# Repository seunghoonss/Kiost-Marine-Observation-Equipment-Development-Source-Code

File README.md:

Kiost Marine Observation Equipment Development Source Code

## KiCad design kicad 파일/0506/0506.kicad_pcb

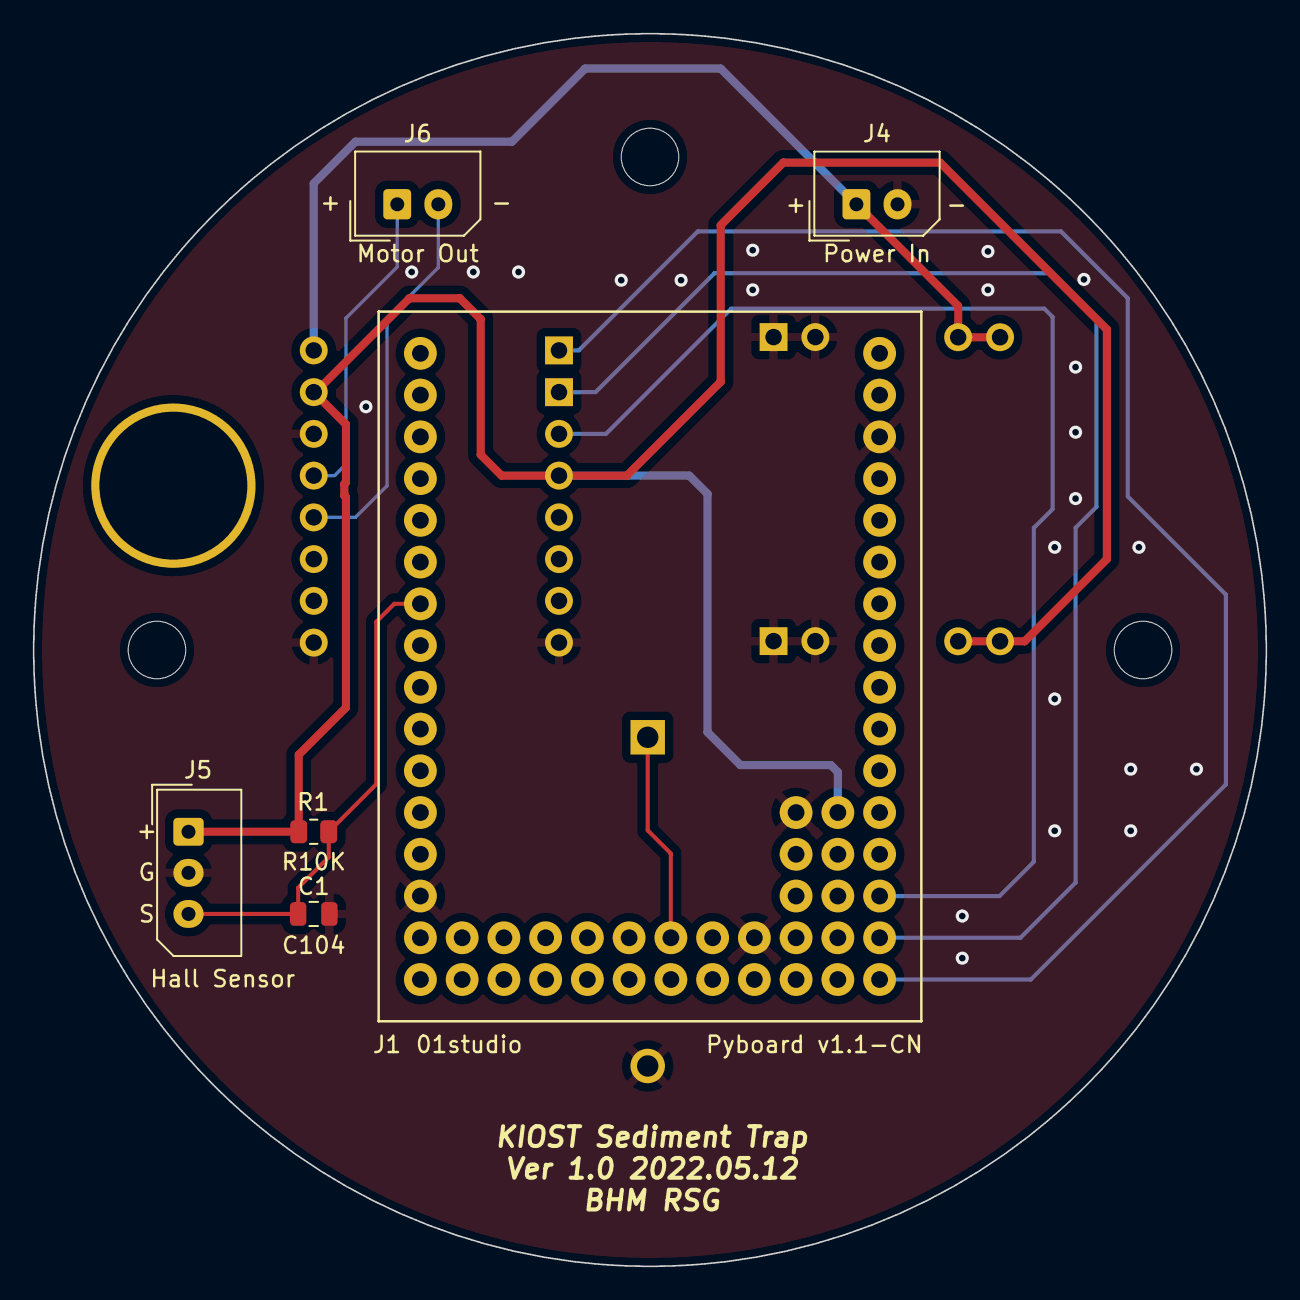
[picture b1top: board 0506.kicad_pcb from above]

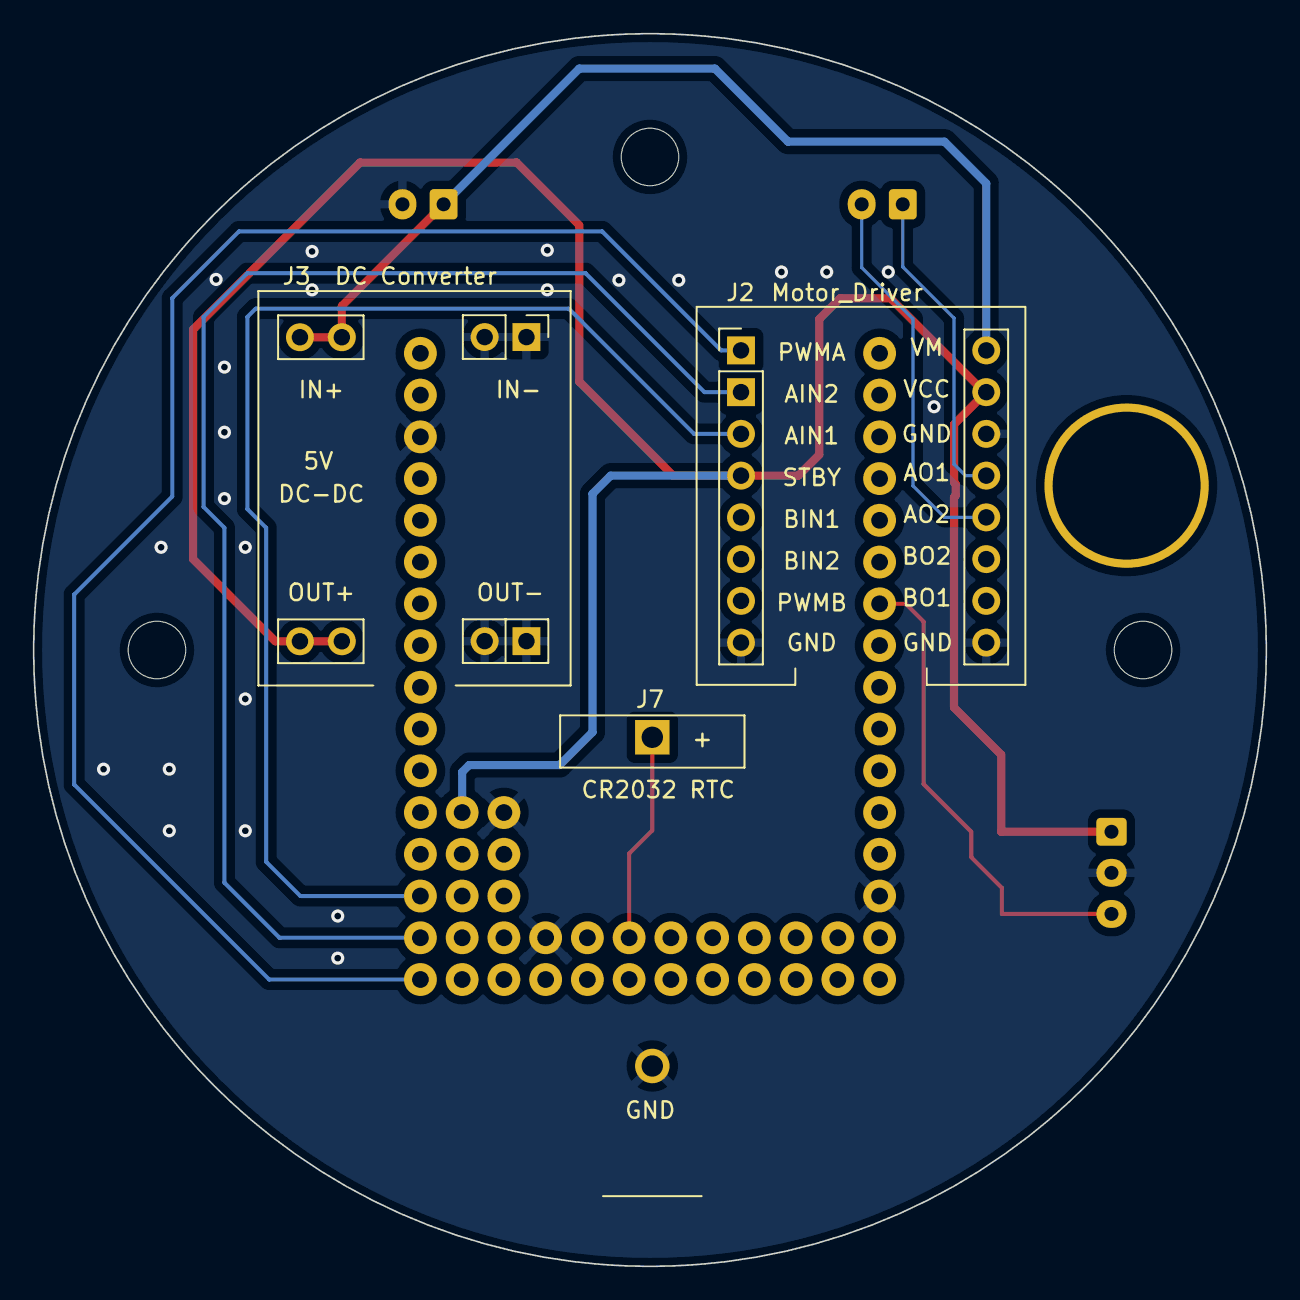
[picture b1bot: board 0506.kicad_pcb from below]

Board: 2 copper layers, 75.0 x 75.0 mm, 13 parts (3 on the bottom side), 10 nets.

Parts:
C1: C104; C_0805_2012Metric
H1: MountingHole_3.2mm_1; MountingHole_3.5mm
H2: MountingHole_3.2mm_2; MountingHole_3.5mm
H3: MountingHole_10mm; Connector Hole 10mm
H4: MountingHole_3.2mm_4; MountingHole_3.5mm
J1: Pyboard v1.1-CN; pyboard_v1.1
J2: Motor_Driver; TB6612FNG
J3: DC Converter; DCDC
J4: Power In; Molex_SPOX_5267-02A_1x02_P2.50mm_Vertical
J5: Hall Sensor; Molex_SPOX_5267-03A_1x03_P2.50mm_Vertical
J6: Motor Out; Molex_SPOX_5267-02A_1x02_P2.50mm_Vertical
J7: CR2032 RTC; BatteryHolder_ComfortableElectronic_CH273-2450_1x2450
R1: R10K; R_0805_2012Metric

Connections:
+5V: J1.P10E (VBAT), J2.4 (STBY), J2.15 (VCC), J3.5 (OUT+), J3.6 (OUT+), J5.1, R1.2
+12V: J2.16 (VMOT), J3.3 (IN+), J3.4 (IN+), J4.1 (12V)
/AIN1: J1.X3 (PA2/TX2/ADC/PWM/SERVO), J2.3 (AIN1)
/AIN2: J1.X2 (PA1/RX4/ADC/PWM/SERVO), J2.2 (AIN2)
/Motor+: J2.13 (AO1), J6.1
/Motor-: J2.12 (AO2), J6.2
/PWMA: J1.X1 (PA0/TX4/ADC/PWM/SERVO), J2.1 (PWMA)
/SIG: C1.1, J1.Y7 (PB14/MISO2/PWM), J5.3, R1.1
GND: C1.2, J1.P8 (GND), J1.P9E (GND), J1.X14 (GND), J1.Y14 (GND), J2.8 (GND), J2.9 (GND), J2.14 (GND), J3.1 (IN-), J3.2 (IN-), J3.7 (OUT-), J3.8 (OUT-), J4.2 (GND), J5.2, J7.2 (-)
unnamed: J1.P6 (VBACK), J7.1 (+)

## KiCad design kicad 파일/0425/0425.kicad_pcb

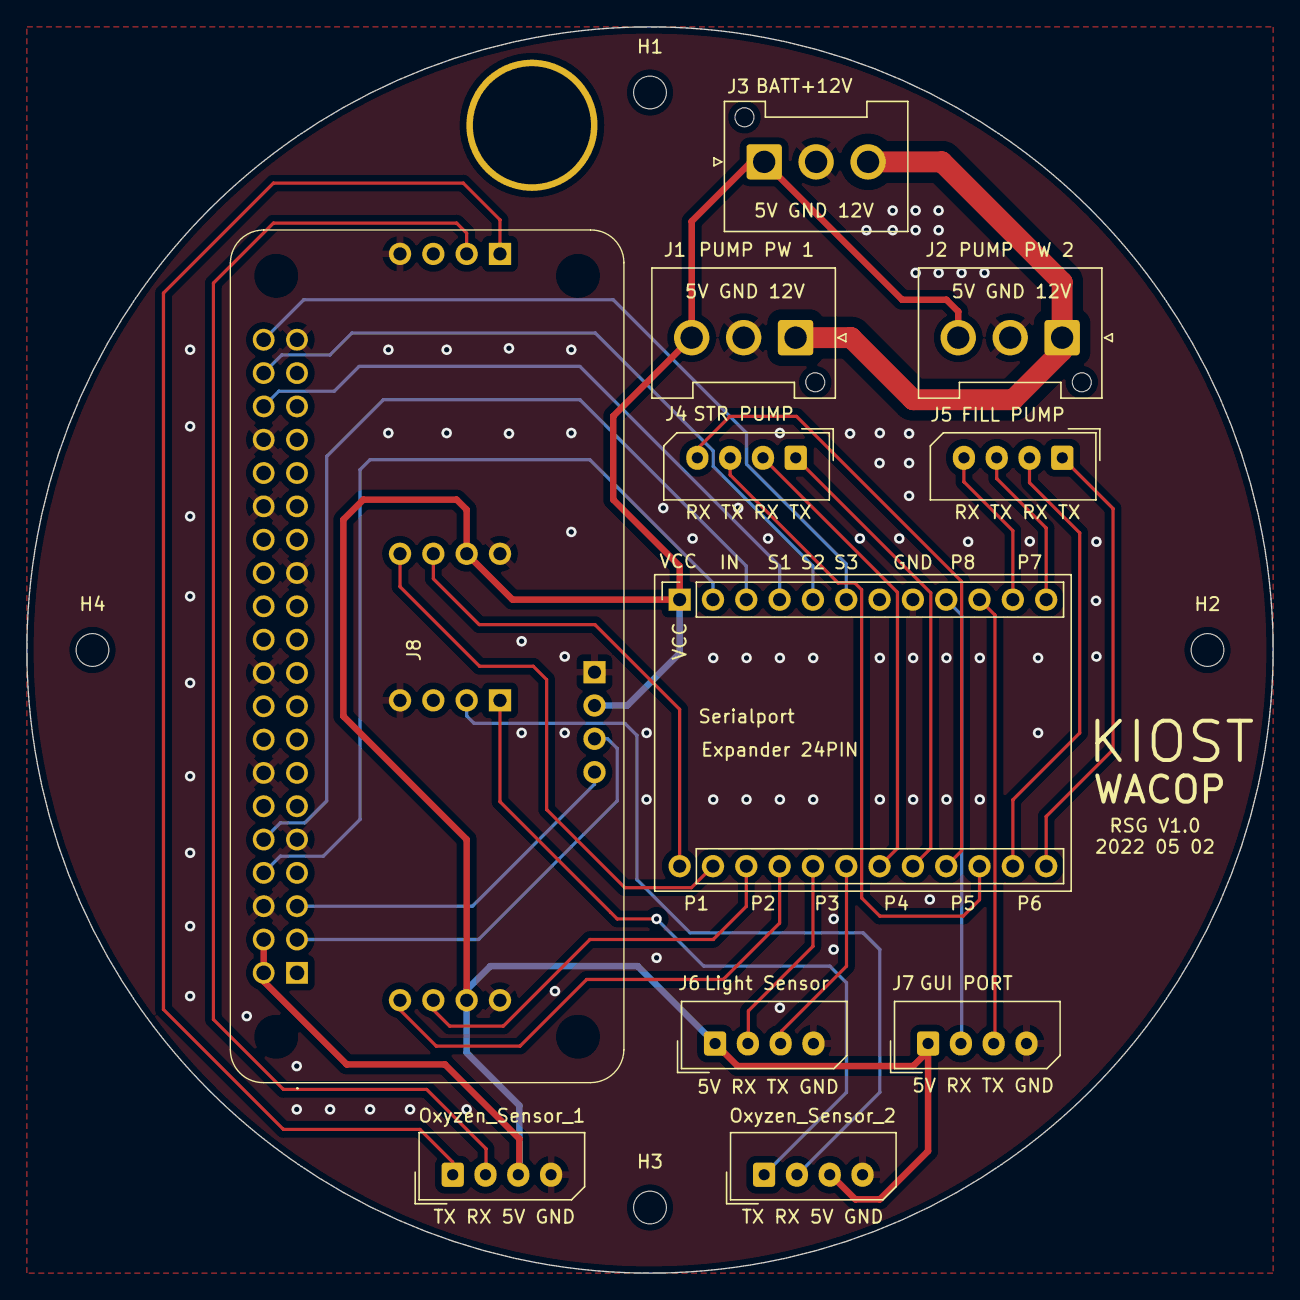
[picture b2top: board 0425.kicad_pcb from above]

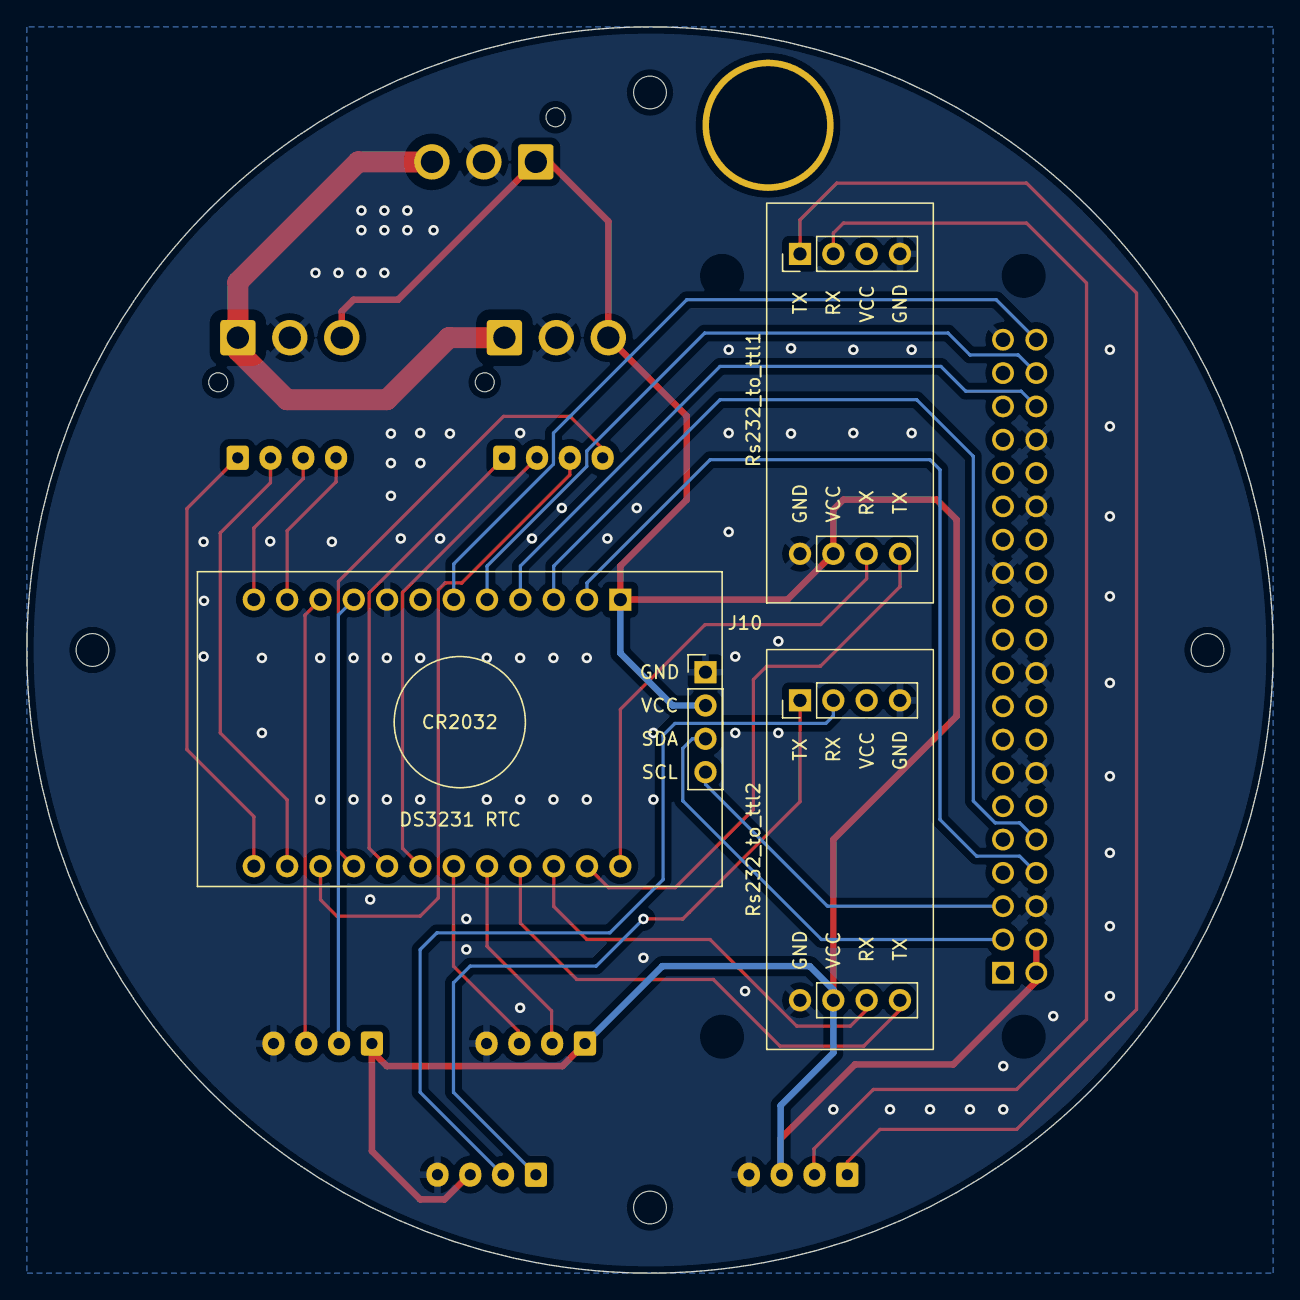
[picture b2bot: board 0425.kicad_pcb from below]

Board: 2 copper layers, 95.0 x 95.0 mm, 19 parts (3 on the bottom side), 30 nets.

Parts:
H1, H2, H3, H4: MH 2.5mm; MountingHole_2.5mm
H5: CH 10mm; Connector Hole 10mm
J1: P_Out_1; JST_VH_B3P-VH-FB-B_1x03_P3.96mm_Vertical
J2: P_Out_2; JST_VH_B3P-VH-FB-B_1x03_P3.96mm_Vertical
J3: Power_IN; JST_VH_B3P-VH-FB-B_1x03_P3.96mm_Vertical
J4: Stir_Motor_RXTX; Molex_SPOX_5267-04A_1x04_P2.50mm_Vertical
J5: Fill_Motor_RXTX; Molex_SPOX_5267-04A_1x04_P2.50mm_Vertical
J6: Light_Sensor; Molex_SPOX_5267-04A_1x04_P2.50mm_Vertical
J7: GUI_PORT; Molex_SPOX_5267-04A_1x04_P2.50mm_Vertical
J8: RaspberryPi_Zero_2_W; Zero_2
J9: SerialPortExpander; serialport expander 2x12pin 2.54mm
J10: Ds3231_RTC; DS3231_RTC
Oxyzen_Sensor_1, Oxyzen_Sensor_2: Conn_01x04; Molex_SPOX_5267-04A_1x04_P2.50mm_Vertical
Rs232_to_ttl1, Rs232_to_ttl2: Conn_02x04_Counter_Clockwise; Rs232 to TTL

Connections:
+5V: J1.3, J2.3, J3.1, J6.1, J7.1, J8.2, J8.4, J9.1 (VCC), J10.2, Oxyzen_Sensor_1.3, Oxyzen_Sensor_2.3, Rs232_to_ttl1.2 (VCC), Rs232_to_ttl2.2 (VCC)
+12V: J1.1, J2.1, J3.3
/RX-IN: J8.8, J9.2 (RX-IN)
/RX-P1: J9.13 (RX-P1), Rs232_to_ttl1.3 (RX)
/RX-P2: J9.15 (RX-P2), Rs232_to_ttl2.3 (RX)
/RX-P3: J6.2, J9.17 (RX-P3)
/RX-P4: J4.2, J9.19 (RX-P4)
/RX-P5: J4.4, J9.21 (RX-P5)
/RX-P6: J5.2, J9.23 (RX-P6)
/RX-P7: J5.4, J9.11 (RX-P7)
/RX-P8: J7.2, J9.9 (RX-P8)
/S1: J8.36, J9.4 (S1)
/S2: J8.38, J9.5 (S2)
/S3: J8.40, J9.6 (S3)
/SCL: J8.5, J10.4
/SDA: J8.3, J10.3
/TX-IN: J8.10, J9.3 (TX)
/TX-P1: J9.14 (TX), Rs232_to_ttl1.4 (TX)
/TX-P2: J9.16 (TX), Rs232_to_ttl2.4 (TX)
/TX-P3: J6.3, J9.18 (TX)
/TX-P4: J4.1, J9.20 (TX)
/TX-P5: J4.3, J9.22 (TX)
/TX-P6: J5.1, J9.24 (TX)
/TX-P7: J5.3, J9.12 (TX)
/TX-P8: J7.3, J9.10 (TX)
GND: J1.2, J2.2, J3.2, J6.4, J7.4, J8.6, J8.9, J8.14, J8.20, J8.25, J8.30, J8.34, J8.39, J9.8 (GND), J10.1, Oxyzen_Sensor_1.4, Oxyzen_Sensor_2.4, Rs232_to_ttl1.1 (GND), Rs232_to_ttl1.5 (GND), Rs232_to_ttl2.1 (GND), Rs232_to_ttl2.5 (GND)
unnamed: Oxyzen_Sensor_1.1, Rs232_to_ttl1.8 (TX)
unnamed: Oxyzen_Sensor_1.2, Rs232_to_ttl1.7 (RX)
unnamed: Oxyzen_Sensor_2.1, Rs232_to_ttl2.8 (TX)
unnamed: Oxyzen_Sensor_2.2, Rs232_to_ttl2.7 (RX)

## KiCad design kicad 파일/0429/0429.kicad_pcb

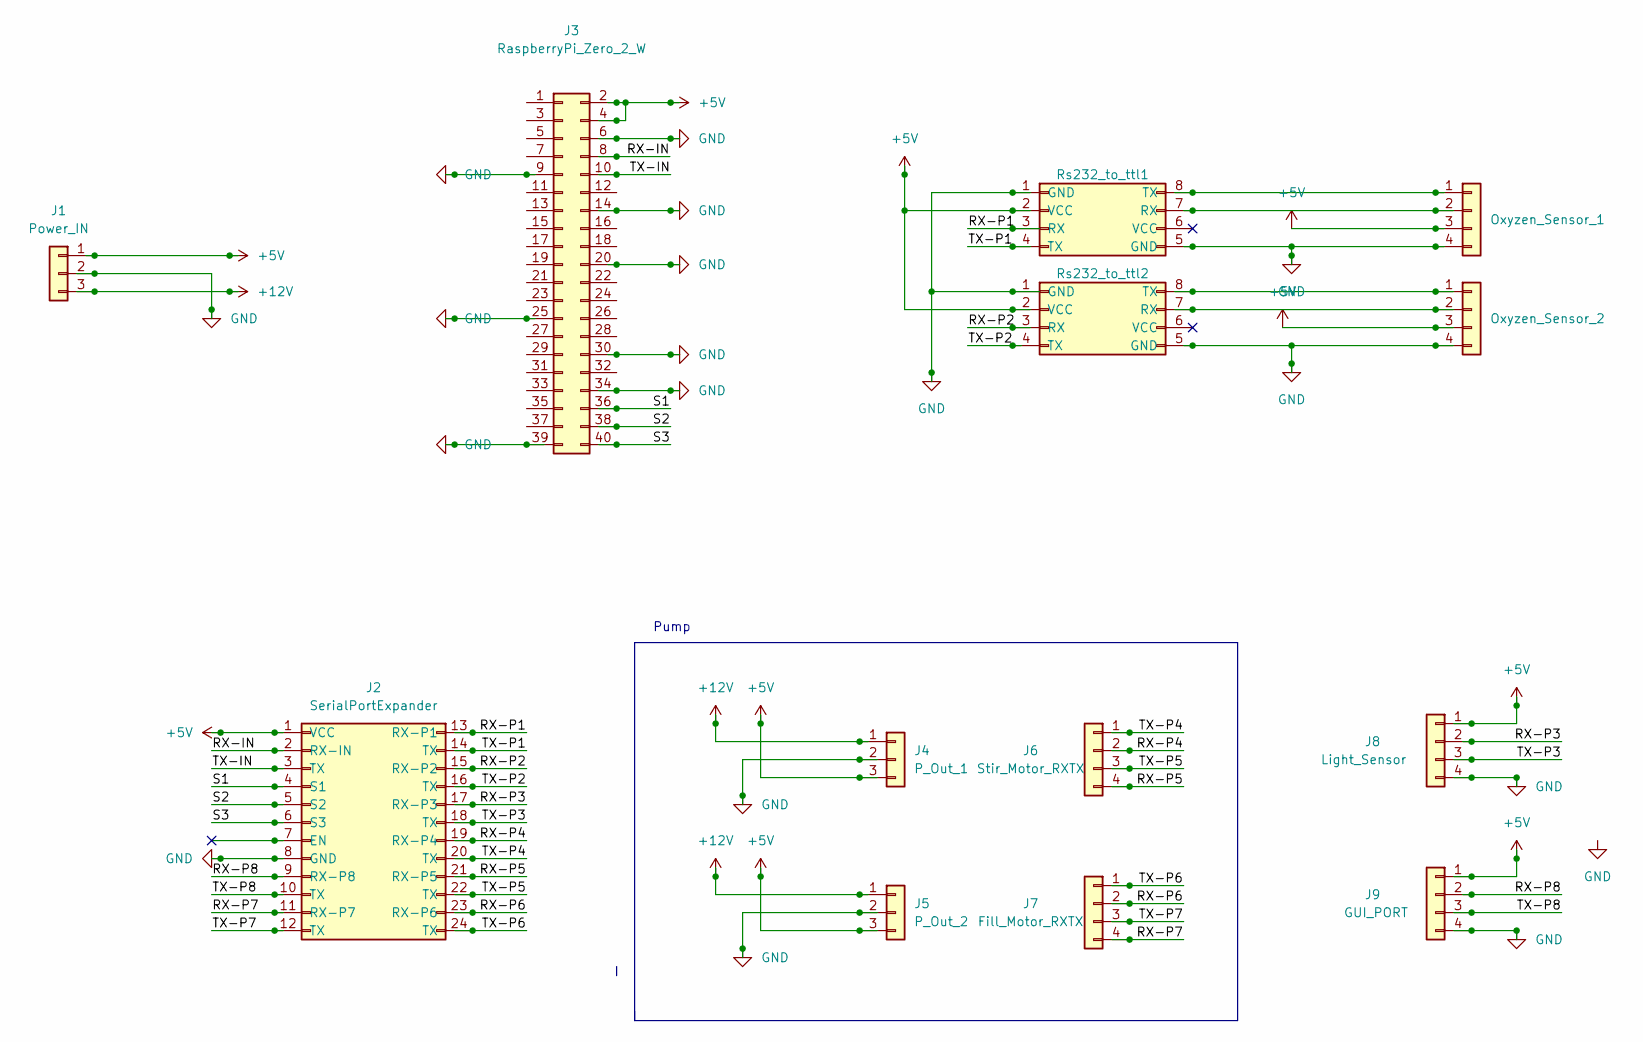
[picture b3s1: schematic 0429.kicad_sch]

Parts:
J1: Power_IN; PinHeader_1x03_P2.54mm_Vertical
J2: SerialPortExpander; serialport expander 2x12pin 2.54mm
J3: RaspberryPi_Zero_2_W; Zero_2
J4: P_Out_1; PinHeader_1x03_P2.54mm_Vertical
J5: P_Out_2; PinHeader_1x03_P2.54mm_Vertical
J6: Stir_Motor_RXTX; PinHeader_1x04_P2.54mm_Vertical
J7: Fill_Motor_RXTX; PinHeader_1x04_P2.54mm_Vertical
J8: Light_Sensor; PinHeader_1x04_P2.54mm_Vertical
J9: GUI_PORT; PinHeader_1x04_P2.54mm_Vertical
Oxyzen_Sensor_1, Oxyzen_Sensor_2: Conn_01x04; PinHeader_1x04_P2.54mm_Vertical
Rs232_to_ttl1, Rs232_to_ttl2: Conn_02x04_Counter_Clockwise; Rs232 to TTL

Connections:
+5V: J1.1, J2.1 (VCC), J3.2, J3.4, J4.3, J5.3, J8.1, J9.1, Oxyzen_Sensor_1.3, Oxyzen_Sensor_2.3, Rs232_to_ttl1.2 (VCC), Rs232_to_ttl2.2 (VCC)
+12V: J1.3, J4.1, J5.1
/RX-IN: J2.2 (RX-IN), J3.8
/RX-P1: J2.13 (RX-P1), Rs232_to_ttl1.3 (RX)
/RX-P2: J2.15 (RX-P2), Rs232_to_ttl2.3 (RX)
/RX-P3: J2.17 (RX-P3), J8.2
/RX-P4: J2.19 (RX-P4), J6.2
/RX-P5: J2.21 (RX-P5), J6.4
/RX-P6: J2.23 (RX-P6), J7.2
/RX-P7: J2.11 (RX-P7), J7.4
/RX-P8: J2.9 (RX-P8), J9.2
/S1: J2.4 (S1), J3.36
/S2: J2.5 (S2), J3.38
/S3: J2.6 (S3), J3.40
/TX-IN: J2.3 (TX), J3.10
/TX-P1: J2.14 (TX), Rs232_to_ttl1.4 (TX)
/TX-P2: J2.16 (TX), Rs232_to_ttl2.4 (TX)
/TX-P3: J2.18 (TX), J8.3
/TX-P4: J2.20 (TX), J6.1
/TX-P5: J2.22 (TX), J6.3
/TX-P6: J2.24 (TX), J7.1
/TX-P7: J2.12 (TX), J7.3
/TX-P8: J2.10 (TX), J9.3
GND: J1.2, J2.8 (GND), J3.6, J3.9, J3.14, J3.20, J3.25, J3.30, J3.34, J3.39, J4.2, J5.2, J8.4, J9.4, Oxyzen_Sensor_1.4, Oxyzen_Sensor_2.4, Rs232_to_ttl1.1 (GND), Rs232_to_ttl1.5 (GND), Rs232_to_ttl2.1 (GND), Rs232_to_ttl2.5 (GND)
unnamed: Oxyzen_Sensor_1.1, Rs232_to_ttl1.8 (TX)
unnamed: Oxyzen_Sensor_1.2, Rs232_to_ttl1.7 (RX)
unnamed: Oxyzen_Sensor_2.1, Rs232_to_ttl2.8 (TX)
unnamed: Oxyzen_Sensor_2.2, Rs232_to_ttl2.7 (RX)

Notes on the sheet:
Pump

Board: 2 copper layers, 13 parts (0 on the bottom side), 28 nets, no tracks yet.

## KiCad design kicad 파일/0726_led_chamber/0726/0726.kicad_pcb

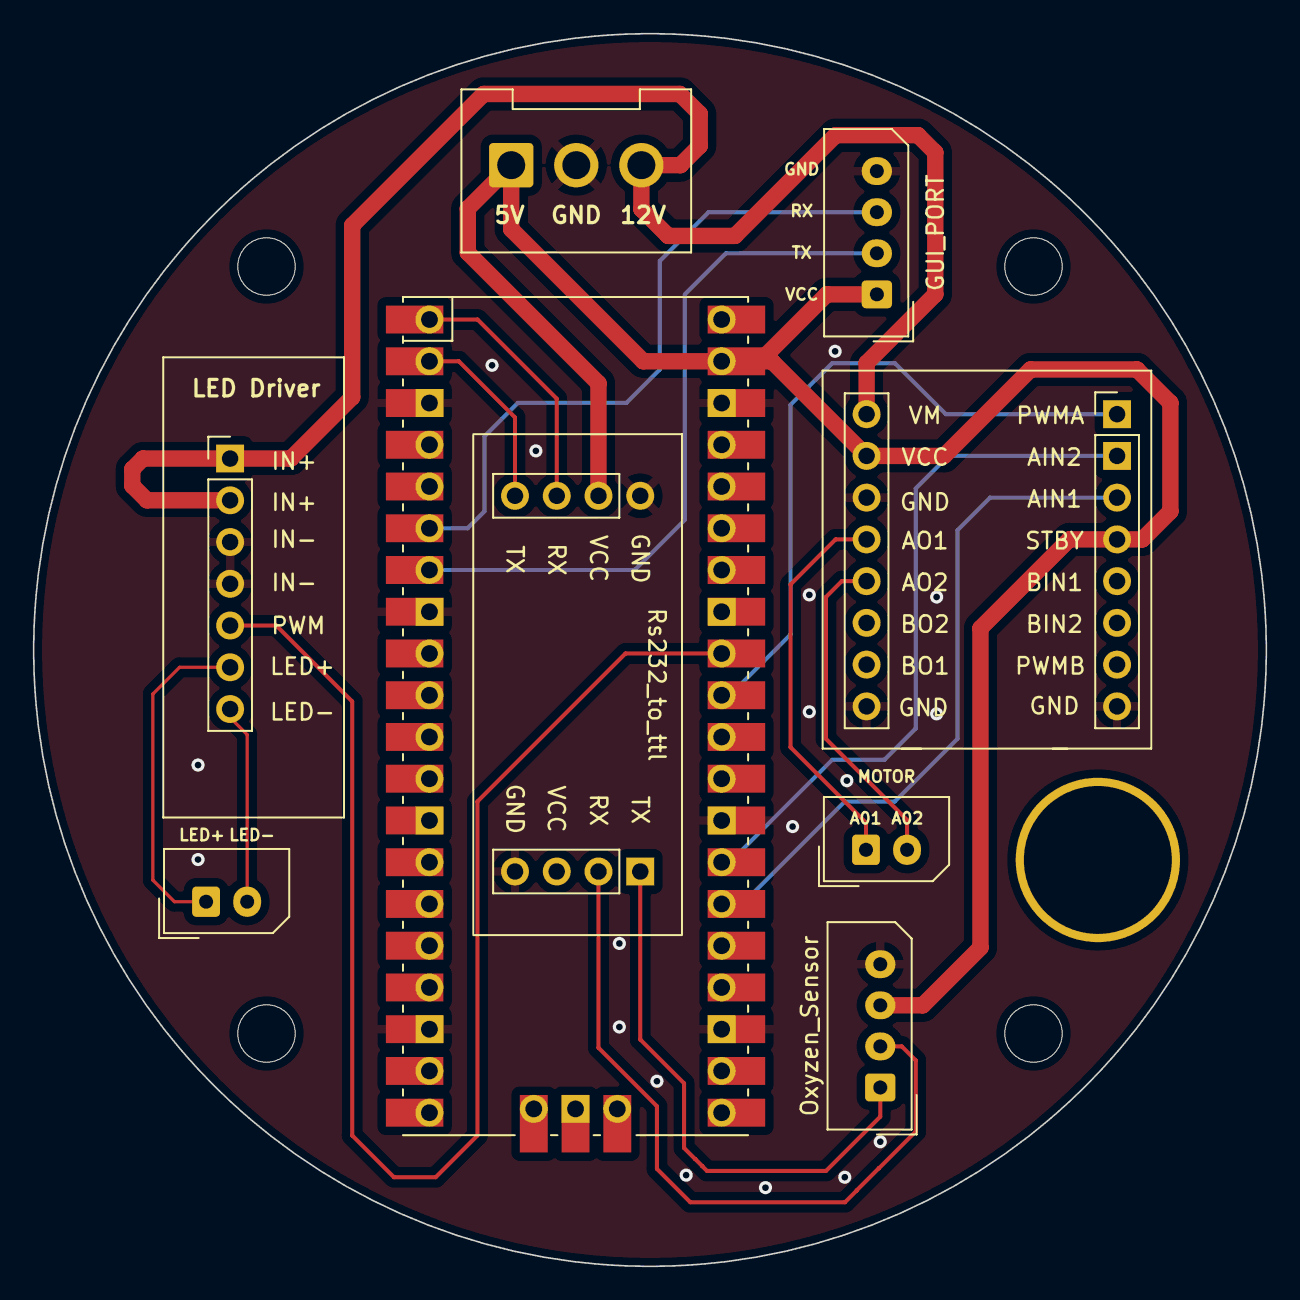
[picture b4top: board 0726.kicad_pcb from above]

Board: 2 copper layers, 75.0 x 75.0 mm, 14 parts (0 on the bottom side), 17 nets.

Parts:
H1, H2, H3, H4: MH 2.5mm; MountingHole_3.5mm
H5: MH 10mm; MountingHole 10mm
J1: LED_01x02; Molex_SPOX_5267-02A_1x02_P2.50mm_Vertical
J2: Power_IN; JST_VH_B3P-VH-FB-B_1x03_P3.96mm_Vertical
J3: LED_DRIVER; JZ led driver
J4: Motor_Drive; TB6612FNG
J5: PUMP_MOTOR_01x02; Molex_SPOX_5267-02A_1x02_P2.50mm_Vertical
J6: GUI_PORT; Molex_SPOX_5267-04A_1x04_P2.50mm_Vertical
Oxyzen_Sensor: Conn_01x04; Molex_SPOX_5267-04A_1x04_P2.50mm_Vertical
Rs232_to_ttl: Conn_02x04_Counter_Clockwise; rs232toTTL
U1: Pico; RPi_Pico_SMD_TH

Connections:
+5V: J2.1, J4.4 (STBY), J4.15 (VCC), J6.1, Oxyzen_Sensor.3, Rs232_to_ttl.2 (VCC), U1.39 (VSYS)
+12V: J2.3, J3.1, J3.2, J4.16 (VMOT)
/AO1: J4.13 (AO1), J5.1
/AO2: J4.12 (AO2), J5.2
/G0: Rs232_to_ttl.3 (RX), U1.1 (GPIO0)
/G1: Rs232_to_ttl.4 (TX), U1.2 (GPIO1)
/G4: J6.3, U1.6 (GPIO4)
/G5: J6.2, U1.7 (GPIO5)
/G20: J4.3 (AIN1), U1.26 (GPIO20)
/G21: J4.2 (AIN2), U1.27 (GPIO21)
/G26: J4.1 (PWMA), U1.31 (GPIO26_ADC0)
/G27: J3.5, U1.32 (GPIO27_ADC1)
/LED+: J1.1, J3.6
/LED-: J1.2, J3.7
GND: J2.2, J3.3, J3.4, J4.8 (GND), J4.9 (GND), J4.14 (GND), J6.4, Oxyzen_Sensor.4, Rs232_to_ttl.1 (GND), Rs232_to_ttl.5 (GND), U1.3 (GND), U1.8 (GND), U1.18 (GND), U1.23 (GND), U1.28 (GND), U1.38 (GND)
unnamed: Oxyzen_Sensor.1, Rs232_to_ttl.8 (TX)
unnamed: Oxyzen_Sensor.2, Rs232_to_ttl.7 (RX)

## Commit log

2023-09-15 Create test
2023-09-15 Rename test to test
